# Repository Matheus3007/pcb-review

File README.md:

# pcb-review

Review the PCBs that [pcb-lab](../pcb-lab) generates in a browser, without KiCad. It's a static web app (no server) that loads a **review bundle** exported from a pcb-lab board:

- **Copper**: 2D view of every copper layer, inner layers included. Pan and zoom, toggle layers, view from the bottom. Click a track, via, pad or zone to highlight its net.
- **Side pane**: the selected net with its components and pins, and each part's **datasheet** in an embedded PDF viewer. The viewer opens at the page for the pin (pin table or pinout), with the pin name highlighted.
- **3D**: the assembled board in three.js, using the real KiCad/EasyEDA STEP models converted to GLB. Tracks and pours show under the solder mask. **X-ray** (key `x`) makes the board translucent and shows every copper layer in its 2D colour. The selected net is drawn on top, with via barrels where it changes layer.
- **BOM** with LCSC/JLC links, and **Checks**: pcb-lab's check report plus KiCad DRC. Click a designator or a DRC marker to jump to it in the copper view.

Deep links work: `#net=CRSF_RX&ref=U1&pin=19`, `#tab=3d`. Several boards can be hosted side by side; `?board=<name>` picks one, and `?bundle=<url>` loads any exported `board.json`.

**Any pcb-lab board, without exporting:** use **Open…**, or drop a board folder (`boards/<name>`), its `build/` folder, or a `.zip` of either anywhere on the page. It is parsed in the browser (`web/src/importer/`, a TypeScript port of the exporter) and nothing is uploaded. Datasheet links, pin pages and 3D models come from the published `bundles/library.json`, built from pcb-lab's part library; parts and models it doesn't know show as LCSC links and boxes.

## Use

```sh
make bundle BOARD=rebot-ctrl-v2     # pcb-lab/boards/<board> -> web/public/bundles/<board>/ (pcb-lab is only read)
make dev                            # http://localhost:5173
make test                           # exporter pytest + web type-check
```

Setup, once: `cd web && npm install`. The exporter's Python environment is created by `uv` on first use. The board has to be built in pcb-lab first (`build/fab/<board>.kicad_pcb`).

Keys in the copper view: `1`..`4` set the active layer, `b` toggles the bottom view, `f` fits the board, `Esc` clears the selection.

## Hosting

Live at **https://review.spinup.fail**, served by GitHub Pages from this repo (`Matheus3007/pcb-review`). It goes live once the DNS record in step 4 exists. The blog stays in `Matheus3007/spinup-fail`. Every push to `main` redeploys. These were the setup steps; 2–4 are done except the DNS record:

1. **What gets public.** `make release-bundle BOARD=x` exports into `bundles/` with `--datasheets link`, so no PDFs are hosted. The side pane shows LCSC's own copy of the PDF in the browser's PDF viewer, opened at the pin's page (e.g. p.56 for PA9). Pin highlighting is only available with bundled PDFs (`DATASHEETS=bundle`, as in local dev). The 3D models (KiCad's library, plus EasyEDA models for the USB-C and LMR36506) are converted and hosted. For box-only 3D, add `ARGS=--no-models`.
2. Commit `bundles/<board>/` and push to `main` in a new GitHub repo, e.g. `Matheus3007/pcb-review`.
   The site opens the `default` board from `bundles/index.json`; change it with `make release-bundle BOARD=x DEFAULT=x`. The others stay in the board selector.
3. In the repo settings, go to *Pages → Source: GitHub Actions*. `.github/workflows/pages.yml` builds `web/`, adds `bundles/`, and deploys.
4. Custom domain:
   - **GitHub:** set the repository variable `PAGES_CNAME=review.spinup.fail` (Settings → Secrets and variables → Actions → Variables). The workflow then writes `CNAME` into the site. Then set the same domain under *Pages → Custom domain* and tick *Enforce HTTPS* once the certificate is issued.
   - **Porkbun DNS:** add a record with type `CNAME`, host `review`, answer `matheus3007.github.io`, TTL 600. Don't touch the apex records the blog uses.
   - Optionally, verify the domain under GitHub *Settings → Pages → Verified domains*: Porkbun gets a `TXT _github-pages-challenge-matheus3007` record. This stops anyone else claiming the subdomain.

## Layout

- `exporter/`: Python (uv). `.kicad_pcb` + netlist + reports + datasheets + STEP models → bundle. See `docs/bundle-format.md`.
- `web/`: Vite + TypeScript (vanilla). Canvas 2D viewer, pdf.js, three.js.
- `scripts/shoot.mjs`: headless screenshots for verification. `screenshots/` holds milestone shots.

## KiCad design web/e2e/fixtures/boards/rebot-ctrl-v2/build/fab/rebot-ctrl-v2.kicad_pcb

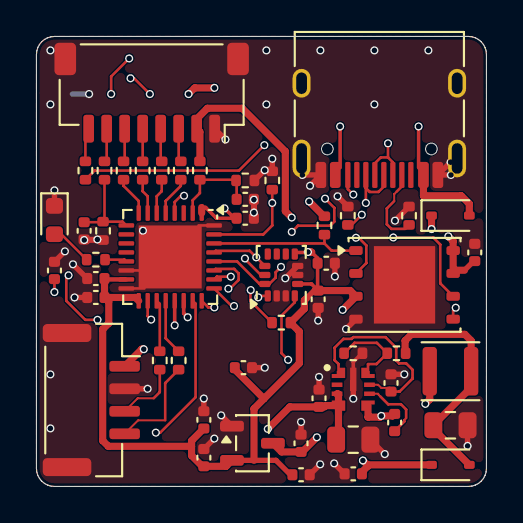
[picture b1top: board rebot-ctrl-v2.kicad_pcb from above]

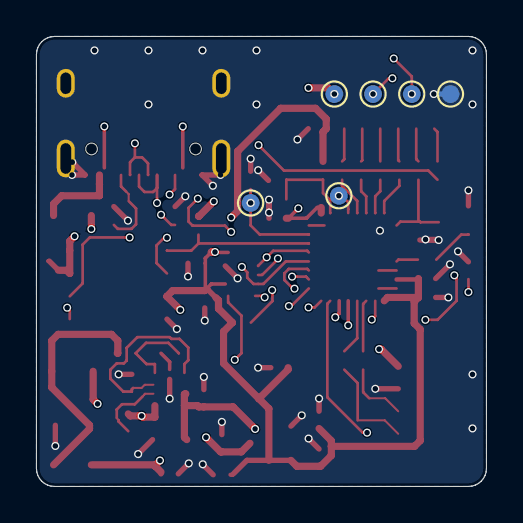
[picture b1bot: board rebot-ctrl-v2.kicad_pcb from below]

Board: 4 copper layers, 25.0 x 25.0 mm, 57 parts (6 on the bottom side), 43 nets.

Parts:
C1: 2.2uF; C_0805_2012Metric
C2, C3, C10, C11, C15, C16, C17, C18, C19, C20, C21: 100nF; C_0402_1005Metric
C4, C7, C8, C14: 1uF; C_0402_1005Metric
C5: 22uF; C_0805_2012Metric
C6, C9, C13: 4.7uF; C_0402_1005Metric
D1, D2: B5819WS 40V 1A; D_SOD-323
D3: red; LED_0603_1608Metric
J1: JST-SH 8P (ESC); JST_SH_SM08B-SRSS-TB_1x08-1MP_P1.00mm_Horizontal
J2: JST-GH 4P (receiver); JST_GH_SM04B-GHS-TB_1x04-1MP_P1.25mm_Horizontal
J3: USB-C 16P; USB_C_Receptacle_HRO_TYPE-C-31-M-12
L1: 22uH 3015; L_Changjiang_FNR3015S
R1, R2, R9, R10, R11, R12: 100; R_0402_1005Metric
R3, R4: 5.1k; R_0402_1005Metric
R5, R13, R15: 100k; R_0402_1005Metric
R6: 22k; R_0402_1005Metric
R7, R14, R16, R18, R19: 10k; R_0402_1005Metric
R8, R17: 1k; R_0402_1005Metric
TP1, TP2, TP3, TP4, TP5, TP6: pad; TestPoint_Pad_D1.0mm
U1: STM32G431KBU6; UFQFPN-32-1EP_5x5mm_P0.5mm_EP3.5x3.5mm
U2: LMR36506 buck; VQFN-HR-9_2x2mm_TI_RPE0009A
U3: XC6206 3.3V; SOT-23-3
U4: LSM6DSV32X; LGA-14_3x2.5mm_P0.5mm_LayoutBorder3x4y
U5: GD25Q128E 16MB; WSON-8-1EP_6x5mm_P1.27mm_EP3.4x4.3mm

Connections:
3V3: C8.1, C9.1, C10.1, C11.1, C13.1, C14.1, C15.1, C19.1, C20.1, C21.1, R18.2, R19.2, TP1.1, U1.1, U1.15, U1.17, U3.2, U4.5, U4.8, U5.3, U5.7, U5.8
+5V: C6.1, C7.1, D1.1, D2.1, J2.1, U3.3
BOOT0: R7.1, TP6.1, U1.31
BUCK_BOOT: C3.1, U2.6
BUCK_FB: R5.2, R6.1, U2.8
BUCK_SW: C3.2, L1.1, U2.5
BUCK_VCC: C4.1, U2.1, U2.7
CC1: J3.A5, R3.1
CC2: J3.B5, R4.1
CRSF_IN: J2.3, R1.1
CRSF_OUT: J2.4, R2.1
CRSF_RX: R1.2, U1.19
CRSF_TX: R2.2, U1.20
CURR_ADC: C17.1, R13.2, R14.1, U1.9
DSHOT1: R9.2, U1.5
DSHOT2: R10.2, U1.6
DSHOT3: R11.2, U1.7
DSHOT4: R12.2, U1.8
ESC_CURR: J1.7, R13.1
ESC_TLM: J1.8, R17.1
FLASH_CS: R19.1, U1.30, U5.1
GND: C1.2, C2.2, C4.2, C5.2, C6.2, C7.2, C8.2, C9.2, C10.2, C11.2, C13.2, C14.2, C15.2, C16.2, C17.2, C18.2, C19.2, C20.2, C21.2, D3.1, J1.1, J1.MP, J2.2, J2.MP, J3.A1, J3.A12, J3.B1, J3.B12, J3.SH, R3.2, R4.2, R6.2, R7.2, R14.2, R16.2, TP2.1, U1.14, U1.16, U1.32, U1.33, U2.9, U3.1, U4.2, U4.3, U4.6, U4.7, U5.4, U5.9
IMU_CS: R18.1, U1.29, U4.12
IMU_INT1: U1.18, U4.4
LED: R8.1, U1.13
LED_A: D3.2, R8.2
M1: J1.3, R9.1
M2: J1.4, R10.1
M3: J1.5, R11.1
M4: J1.6, R12.1
NRST: C16.1, TP5.1, U1.4
SPI_MISO: U1.27, U4.1, U5.2
SPI_MOSI: U1.28, U4.14, U5.5
SPI_SCK: U1.26, U4.13, U5.6
SWCLK: TP4.1, U1.24
SWDIO: TP3.1, U1.23
TLM_RX: R17.2, U1.25
USB_DM: J3.A7, J3.B7, U1.21
USB_DP: J3.A6, J3.B6, U1.22
V5_BUCK: C5.1, D1.2, L1.2, R5.1
VBAT: C1.1, C2.1, J1.2, R15.1, U2.3, U2.4
VBAT_ADC: C18.1, R15.2, R16.1, U1.2
VBUS: D2.2, J3.A4, J3.A9, J3.B4, J3.B9
